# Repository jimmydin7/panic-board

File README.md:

The panic board is a small 4-buttons macropad for shortcuts. It consists 3 switches that will act as Copy, Paste, and Cut + a rotary encoder for the volume! It is powered by a Xiao-RP-2040

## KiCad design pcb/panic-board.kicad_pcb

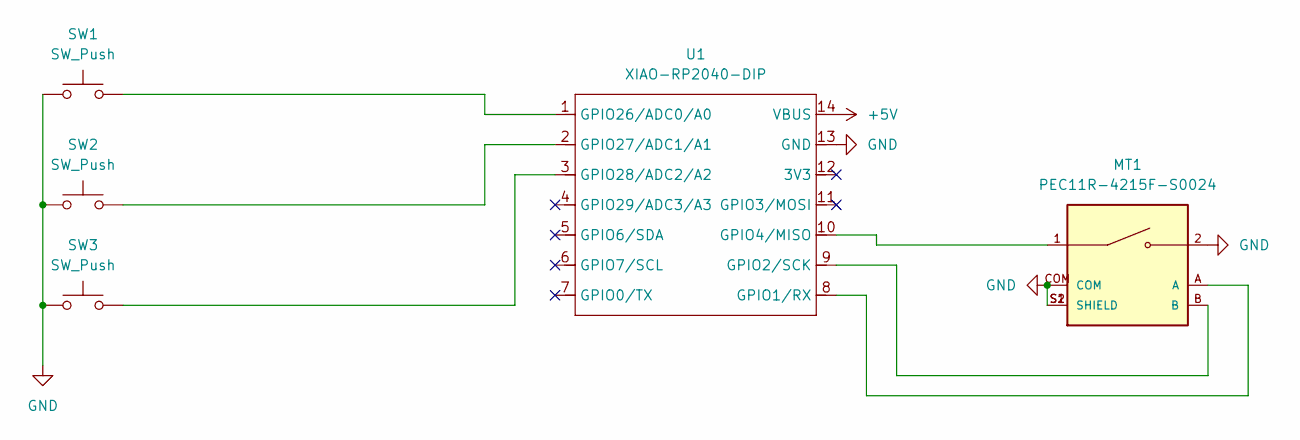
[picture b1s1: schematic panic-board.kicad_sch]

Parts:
MT1: PEC11R-4215F-S0024; XDCR_PEC11R-4215F-S0024; PARTREV Rev. 09/19
SW1, SW2, SW3: SW_Push; SW_Cherry_MX_1.00u_PCB
U1: XIAO-RP2040-DIP

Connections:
+5V: U1.14 (VBUS)
GND: MT1.2, MT1.COM, MT1.S1 (SHIELD), MT1.S2 (SHIELD), SW1.1, SW2.1, SW3.1, U1.13 (GND)
unnamed: MT1.A, U1.8 (GPIO1/RX)
unnamed: MT1.B, U1.9 (GPIO2/SCK)
unnamed: MT1.1, U1.10 (GPIO4/MISO)
unnamed: SW1.2, U1.1 (GPIO26/ADC0/A0)
unnamed: SW2.2, U1.2 (GPIO27/ADC1/A1)
unnamed: SW3.2, U1.3 (GPIO28/ADC2/A2)

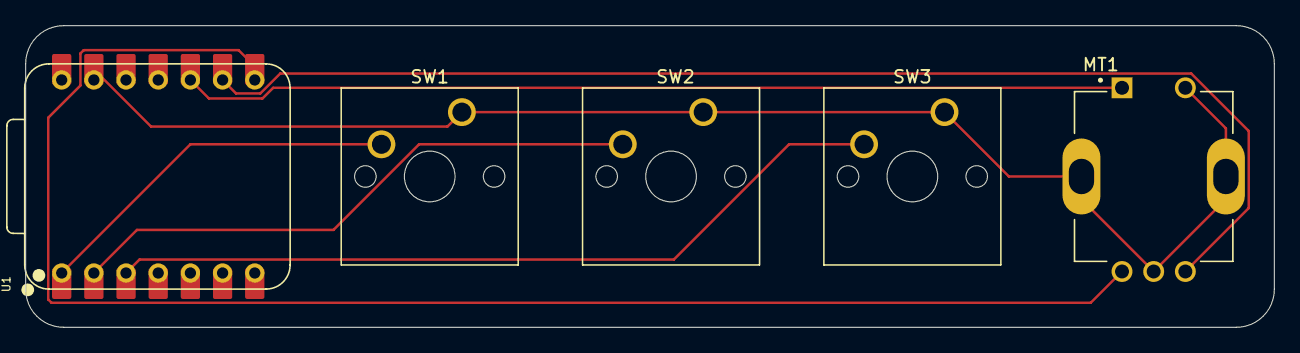
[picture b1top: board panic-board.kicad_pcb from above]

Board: 2 copper layers, 98.6 x 23.8 mm, 5 parts (0 on the bottom side), 7 nets.

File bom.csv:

Designator,Footprint,Quantity,Value,Price (total),
,,,,,
MT1,PEC11R-4215F-S0024,1,PEC11R-4215F-S0024,$0.99,https://www.aliexpress.com/item/1005009189427630.html?spm=a2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
"SW1, SW2, SW3",SW_Cherry_MX_1.00u_PCB,3,SW_Push,$2.48 (10-pack),https://www.aliexpress.com/item/1005006255961111.html?spm=a2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
U1,XIAO-RP2040-DIP,1,XIAO-RP2040-DIP,$5.56,https://www.aliexpress.com/item/1005008200917480.html?spm=a2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
PCB,(JLCPCB),1,,$4.47,
EC11 keycap,,1,,$3.14,https://www.aliexpress.com/item/1005008686516265.html?spm=a2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
,,,,Total aliexpress (with shipping & vat): ~$ $17.45,
,,,,Total JLCPCB (with shipping & vat): ~$4.47,
,,,,Grand total (with shipping): ~$21.92,
,,,,"I couldn't find keycaps for switches, if you have a link for affordable ones please add them to the grand and specify the link!",

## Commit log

2025-10-06 add images!
2025-10-06 upload pcb files
2025-10-08 add bom
